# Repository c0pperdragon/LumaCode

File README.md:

# LumaCode
Definition of the "LumaCode" signal standard and documentation of various implementations.

* [Documentation wiki](https://github.com/c0pperdragon/LumaCode/wiki)
* [Issue tracking](https://github.com/c0pperdragon/LumaCode/issues)
* [Reference implementation](signalgenerator)

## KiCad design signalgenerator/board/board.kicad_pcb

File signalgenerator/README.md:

# Signal generator

A small device intended to generate various LumaCode signals. Its main purpose is for developing and
testing decoding/upscaling equipment.

## Usage

The device is powered by 5V over a barrel jack (center positive).
Use the jumper link to select a 50Hz (when jumper closed) or 60Hz (when jumper open) source. 
16 different patterns can be chosen by the 16 combinations of the dip switches.

## Signal possibilites 

The following switch combinations are supported:

1   |  2  | 3   |4    | Signal
--- | --- | --- | --- | -------------------------
OFF | OFF | OFF | OFF | C64/C128
OFF | OFF | OFF | ON  | C64 6567R56A (only 60Hz)
OFF | OFF | ON  | OFF | VIC 20 
OFF | OFF | ON  | ON  | C16, Plus/4
OFF | ON  | OFF | OFF | Atari 8-bit
OFF | ON  | OFF | ON  | Atari 2600 PAL colors
OFF | ON  | ON  | OFF | Atari 2600 NTSC colors
OFF | ON  | ON  | ON  | Atari 7800 
ON  | OFF | OFF | OFF | TMS99xxA
ON  | OFF | OFF | ON  | ZX Spectrum
ON  | OFF | ON  | OFF | NES
ON  | OFF | ON  | ON  | Sega Master System
ON  | ON  | OFF | OFF | Intellivision
ON  | ON  | OFF | ON  | G7000 or Odyssey II
ON  | ON  | ON  | OFF | MC6847
ON  | ON  | ON  | ON  | Lumacode 270p (only 50Hz)

The last option is not used in any actual hardware, but this is an experimental signal with a resolution 
of 480x270 and 6 bits color depth (same color encoding as the Master System). When upscaling by a 
factor of 4, this signal perfectly fits a full-HD screen. Maybe this could be
useful for some tinkering projects.

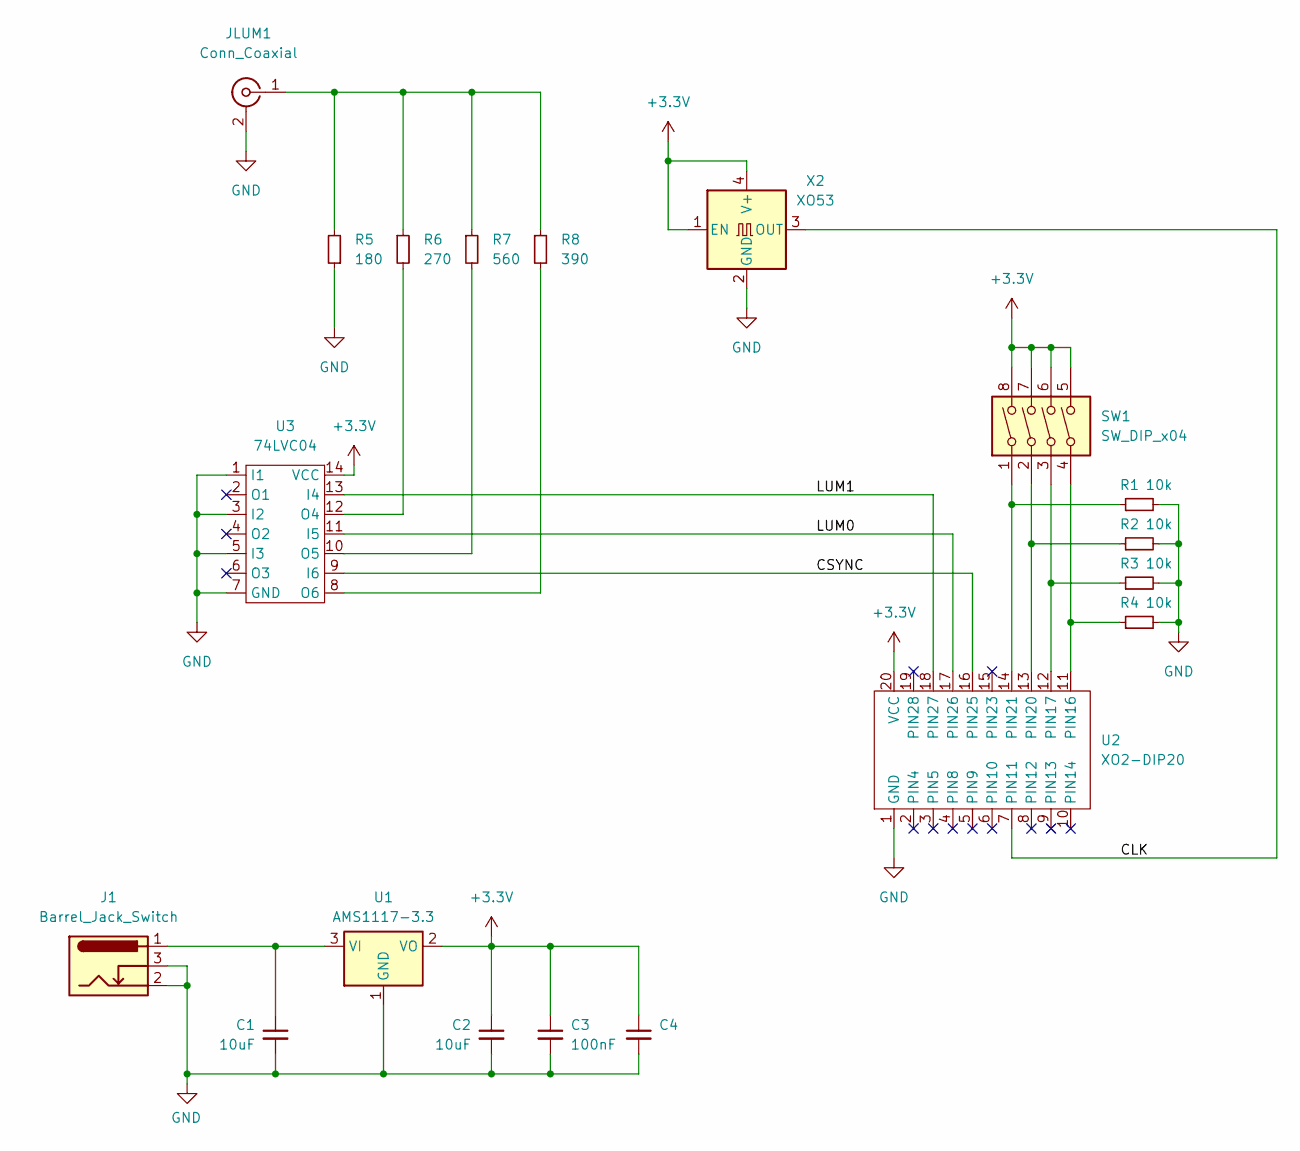
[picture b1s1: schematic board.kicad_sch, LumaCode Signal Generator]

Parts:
C1, C2: 10uF; C_0805_2012Metric_Pad1.18x1.45mm_HandSolder
C3, C4: 100nF; C_0603_1608Metric_Pad1.08x0.95mm_HandSolder
J1: Barrel_Jack_Switch; BarrelJack_Horizontal
JLUM1: Conn_Coaxial; RCA_JACK
R1, R2, R3, R4: 10k; R_0805_2012Metric_Pad1.20x1.40mm_HandSolder
R5: 180; R_0805_2012Metric_Pad1.20x1.40mm_HandSolder
R6: 270; R_0805_2012Metric_Pad1.20x1.40mm_HandSolder
R7: 560; R_0805_2012Metric_Pad1.20x1.40mm_HandSolder
R8: 390; R_0805_2012Metric_Pad1.20x1.40mm_HandSolder
SW1: SW_DIP_x04; DIP-8_W7.62mm
U1: AMS1117-3.3; SOT-223-3_TabPin2
U2: XO2-DIP20; DIP-20_W7.62mm
U3: 74LVC04; TSSOP-14_4.4x5mm_P0.65mm
X2: XO53; Oscillator_SMD_EuroQuartz_XO53-4Pin_5.0x3.2mm

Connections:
+3.3V: C2.1, C3.1, C4.1, SW1.5, SW1.6, SW1.7, SW1.8, U1.2 (VO), U2.20 (VCC), U3.14 (VCC), X2.1 (EN), X2.4 (V+)
/CLK: U2.7 (PIN11), X2.3 (OUT)
/CSYNC: U2.16 (PIN25), U3.9 (I6)
/LUM0: U2.17 (PIN26), U3.11 (I5)
/LUM1: U2.18 (PIN27), U3.13 (I4)
GND: C1.2, C2.2, C3.2, C4.2, J1.2, J1.3, JLUM1.2 (Ext), R1.2, R2.2, R3.2, R4.2, R5.1, U1.1 (GND), U2.1 (GND), U3.1 (I1), U3.3 (I2), U3.5 (I3), U3.7 (GND), X2.2 (GND)
unnamed: JLUM1.1 (In), R5.2, R6.1, R7.1, R8.1
unnamed: C1.1, J1.1, U1.3 (VI)
unnamed: R4.1, SW1.4, U2.11 (PIN16)
unnamed: R3.1, SW1.3, U2.12 (PIN17)
unnamed: R2.1, SW1.2, U2.13 (PIN20)
unnamed: R1.1, SW1.1, U2.14 (PIN21)
unnamed: R6.2, U3.12 (O4)
unnamed: R7.2, U3.10 (O5)
unnamed: R8.2, U3.8 (O6)

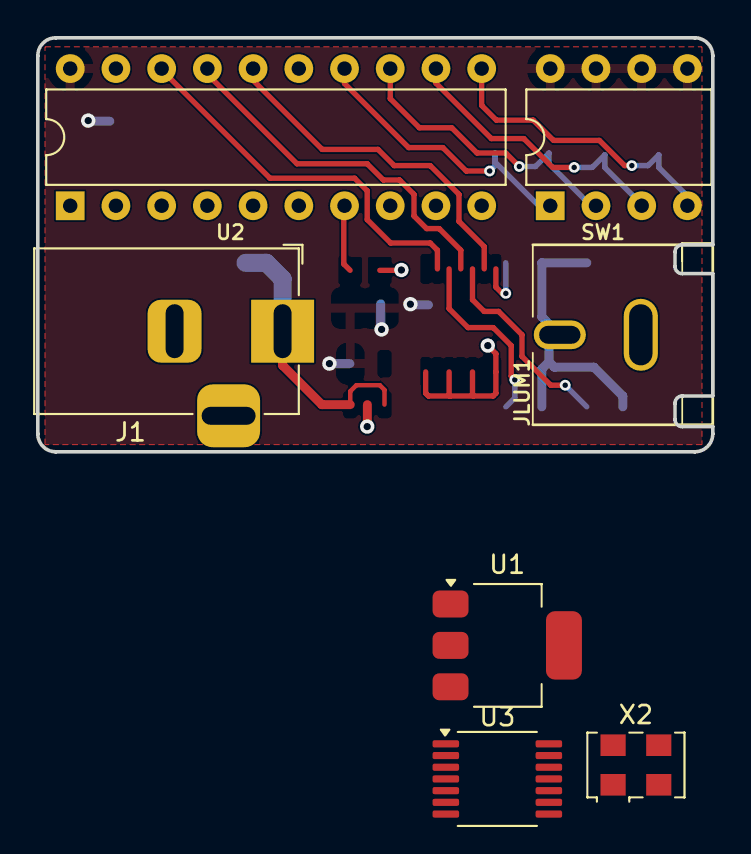
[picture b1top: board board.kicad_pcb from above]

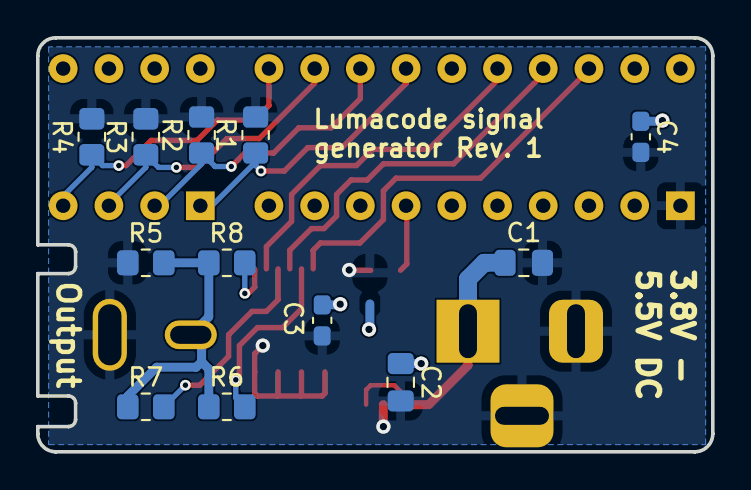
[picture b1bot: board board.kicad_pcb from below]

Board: 2 copper layers, 37.5 x 23.0 mm, 19 parts (12 on the bottom side), 15 nets.

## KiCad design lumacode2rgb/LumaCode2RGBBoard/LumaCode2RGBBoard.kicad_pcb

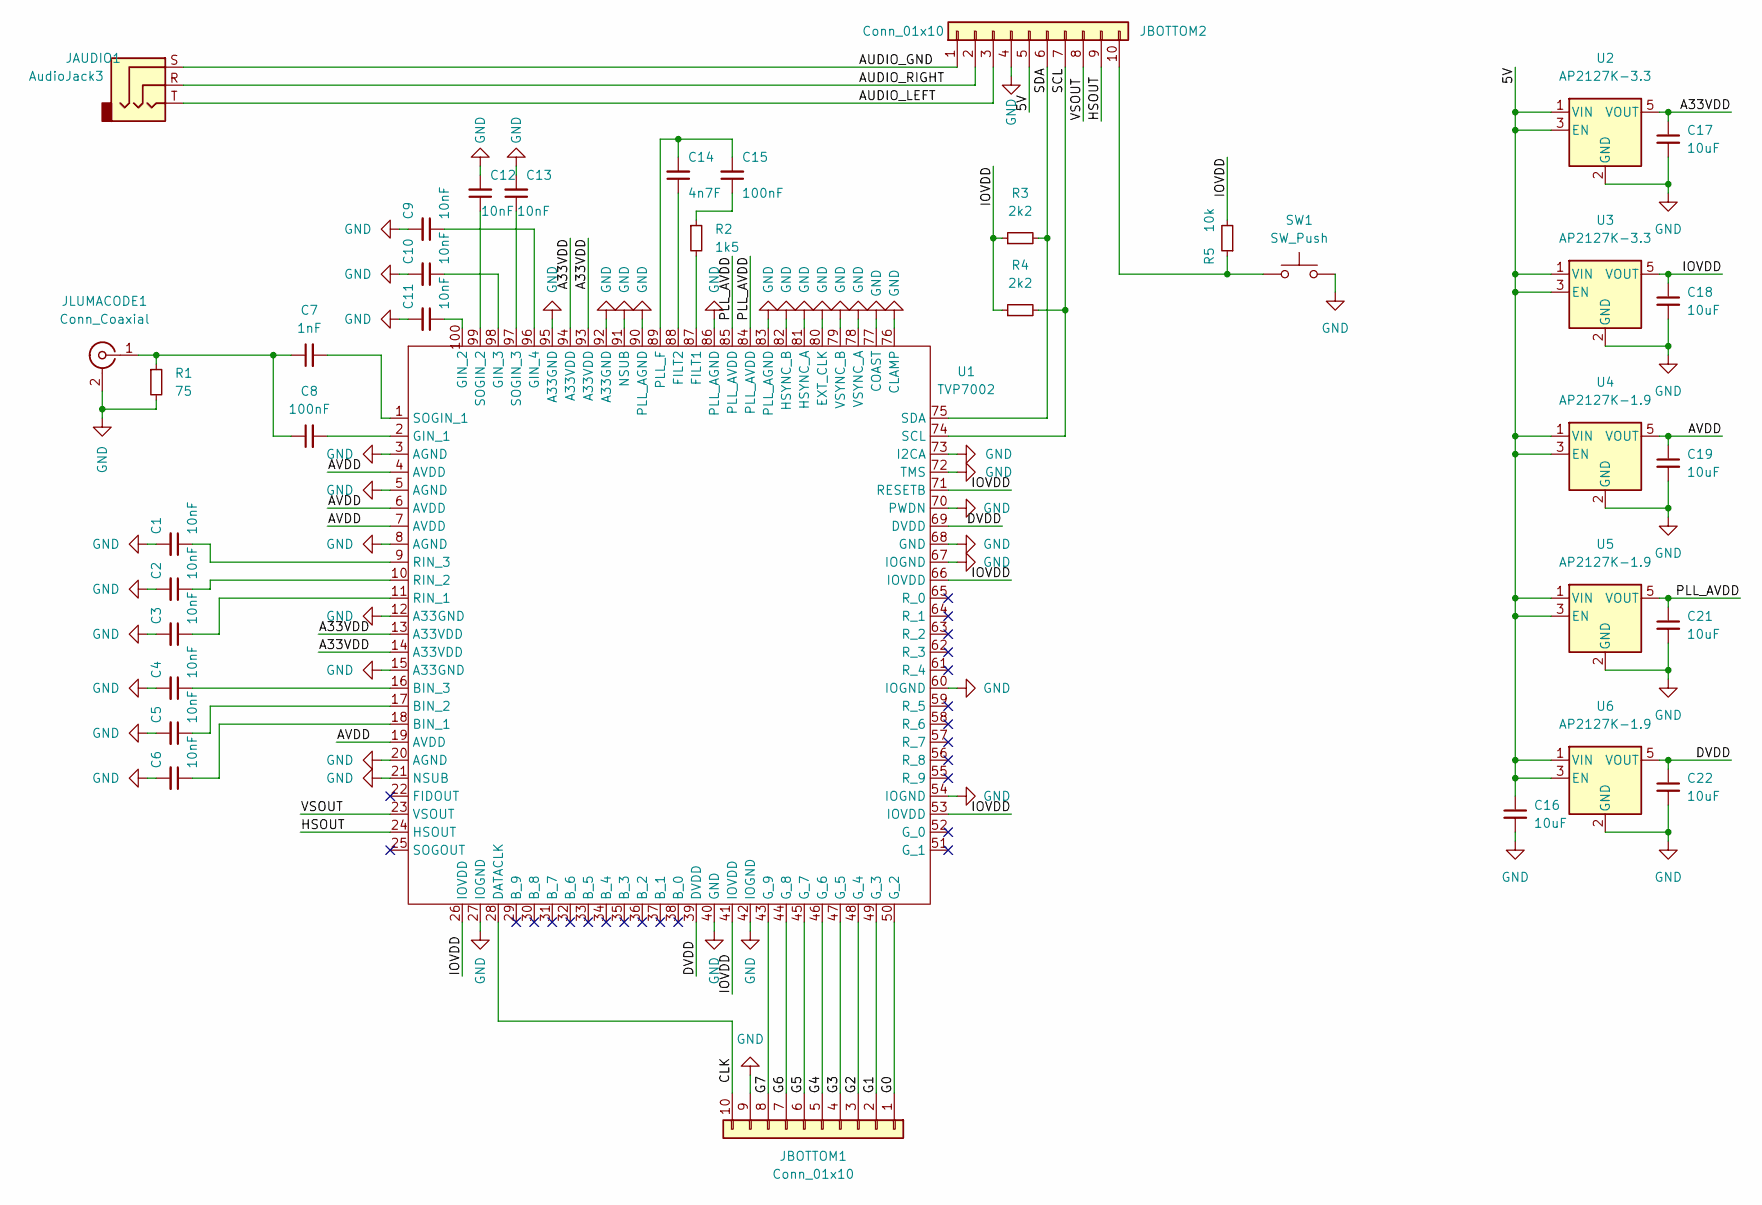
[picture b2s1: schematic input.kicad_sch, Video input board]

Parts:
C1, C2, C3, C4, C5, C6, C9, C10, C11, C12, C13: 10nF; C_0603_1608Metric
C7: 1nF; C_0603_1608Metric
C8, C15: 100nF; C_0603_1608Metric
C14: 4n7F; C_0603_1608Metric
C16, C17, C18, C19, C21, C22: 10uF; C_0805_2012Metric
JAUDIO1: AudioJack3; Jack_3.5mm_Lumberg_1503_07_Horizontal
JBOTTOM1, JBOTTOM2: Conn_01x10; PinHeader_1x10_P2.54mm_Vertical
JLUMACODE1: Conn_Coaxial; RCA_JACK
R1: 75; R_0805_2012Metric
R2: 1k5; R_0805_2012Metric
R3, R4: 2k2; R_0805_2012Metric
R5: 10k; R_0805_2012Metric
SW1: SW_Push; SW_Tactile_SKHH_Angled
U1: TVP7002; TQFP-100-1EP_14x14mm_P0.5mm_EP5x5mm
U2, U3: AP2127K-3.3; SOT-23-5
U4, U5, U6: AP2127K-1.9; SOT-23-5

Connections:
/Input/5V: C16.1, JBOTTOM2.5, U2.1 (VIN), U2.3 (EN), U3.1 (VIN), U3.3 (EN), U4.1 (VIN), U4.3 (EN), U5.1 (VIN), U5.3 (EN), U6.1 (VIN), U6.3 (EN)
/Input/A33VDD: C17.1, U1.13 (A33VDD), U1.14 (A33VDD), U1.93 (A33VDD), U1.94 (A33VDD), U2.5 (VOUT)
/Input/AUDIO_GND: JAUDIO1.S, JBOTTOM2.1
/Input/AUDIO_LEFT: JAUDIO1.T, JBOTTOM2.3
/Input/AUDIO_RIGHT: JAUDIO1.R, JBOTTOM2.2
/Input/AVDD: C19.1, U1.4 (AVDD), U1.6 (AVDD), U1.7 (AVDD), U1.19 (AVDD), U4.5 (VOUT)
/Input/CLK: JBOTTOM1.10, U1.28 (DATACLK)
/Input/DVDD: C22.1, U1.39 (DVDD), U1.69 (DVDD), U6.5 (VOUT)
/Input/G0: JBOTTOM1.1, U1.50 (G_2)
/Input/G1: JBOTTOM1.2, U1.49 (G_3)
/Input/G2: JBOTTOM1.3, U1.48 (G_4)
/Input/G3: JBOTTOM1.4, U1.47 (G_5)
/Input/G4: JBOTTOM1.5, U1.46 (G_6)
/Input/G5: JBOTTOM1.6, U1.45 (G_7)
/Input/G6: JBOTTOM1.7, U1.44 (G_8)
/Input/G7: JBOTTOM1.8, U1.43 (G_9)
/Input/HSOUT: JBOTTOM2.9, U1.24 (HSOUT)
/Input/IOVDD: C18.1, R3.1, R4.1, R5.2, U1.26 (IOVDD), U1.41 (IOVDD), U1.53 (IOVDD), U1.66 (IOVDD), U1.71 (RESETB), U3.5 (VOUT)
/Input/PLL_AVDD: C21.1, U1.84 (PLL_AVDD), U1.85 (PLL_AVDD), U5.5 (VOUT)
/Input/SCL: JBOTTOM2.7, R4.2, U1.74 (SCL)
/Input/SDA: JBOTTOM2.6, R3.2, U1.75 (SDA)
/Input/VSOUT: JBOTTOM2.8, U1.23 (VSOUT)
GND: C1.2, C2.2, C3.2, C4.2, C5.2, C6.2, C9.2, C10.2, C11.2, C12.2, C13.2, C16.2, C17.2, C18.2, C19.2, C21.2, C22.2, JBOTTOM1.9, JBOTTOM2.4, JLUMACODE1.2 (Ext), R1.2, SW1.2, U1.3 (AGND), U1.5 (AGND), U1.8 (AGND), U1.12 (A33GND), U1.15 (A33GND), U1.20 (AGND), U1.21 (NSUB), U1.27 (IOGND), U1.40 (GND), U1.42 (IOGND), U1.54 (IOGND), U1.60 (IOGND), U1.67 (IOGND), U1.68 (GND), U1.70 (PWDN), U1.72 (TMS), U1.73 (I2CA), U1.76 (CLAMP), U1.77 (COAST), U1.78 (VSYNC_A), U1.79 (VSYNC_B), U1.80 (EXT_CLK), U1.81 (HSYNC_A), U1.82 (HSYNC_B), U1.83 (PLL_AGND), U1.86 (PLL_AGND), U1.90 (PLL_AGND), U1.91 (NSUB), U1.92 (A33GND), U1.95 (A33GND), U2.2 (GND), U3.2 (GND), U4.2 (GND), U5.2 (GND), U6.2 (GND); also elsewhere on the board
unnamed: C1.1, U1.9 (RIN_3)
unnamed: C2.1, U1.10 (RIN_2)
unnamed: C3.1, U1.11 (RIN_1)
unnamed: C4.1, U1.16 (BIN_3)
unnamed: C5.1, U1.17 (BIN_2)
unnamed: C6.1, U1.18 (BIN_1)
unnamed: C7.1, C8.1, JLUMACODE1.1 (In), R1.1
unnamed: C7.2, U1.1 (SOGIN_1)
unnamed: C8.2, U1.2 (GIN_1)
unnamed: C9.1, U1.96 (GIN_4)
unnamed: C10.1, U1.98 (GIN_3)
unnamed: C11.1, U1.100 (GIN_2)
unnamed: C12.1, U1.99 (SOGIN_2)
unnamed: C13.1, U1.97 (SOGIN_3)
unnamed: C14.1, U1.88 (FILT2)
unnamed: C14.2, C15.2, U1.89 (PLL_F)
unnamed: C15.1, R2.1
unnamed: JBOTTOM2.10, R5.1, SW1.1
unnamed: R2.2, U1.87 (FILT1)

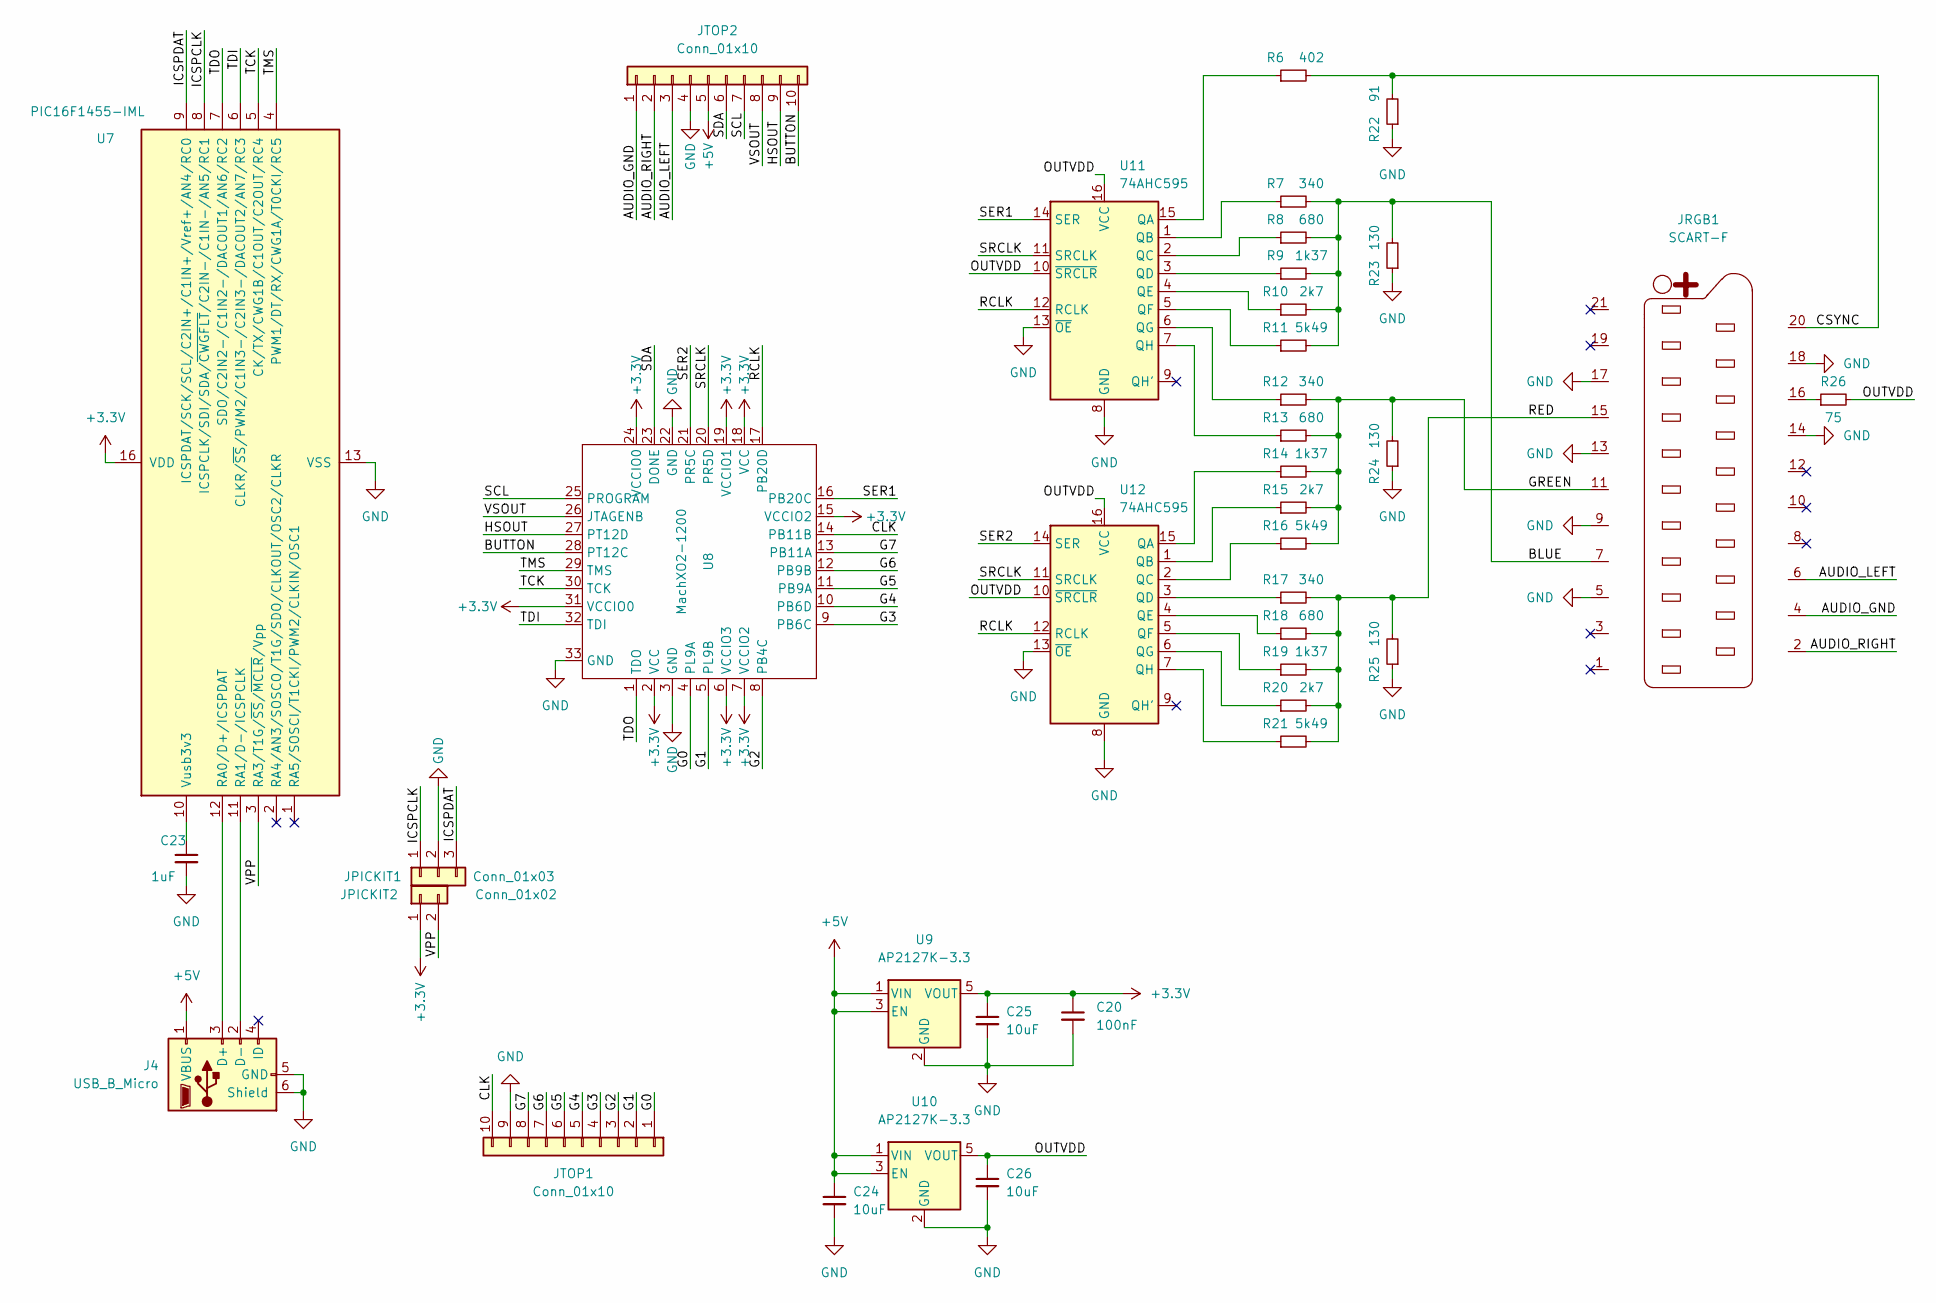
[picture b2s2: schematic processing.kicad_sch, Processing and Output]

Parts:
C20: 100nF; C_0603_1608Metric
C23: 1uF; C_0805_2012Metric
C24, C25, C26: 10uF; C_0805_2012Metric
J4: USB_B_Micro; USB_Micro-B_Amphenol_10104110_Horizontal
JPICKIT1: Conn_01x03; PinHeader_1x03_P2.54mm_Vertical
JPICKIT2: Conn_01x02; PinHeader_1x02_P2.54mm_Vertical
JRGB1: SCART-F; SCART_Edge_mount
JTOP1, JTOP2: Conn_01x10; PinHeader_1x10_P2.54mm_Vertical
R6: 402; R_0603_1608Metric
R7, R12, R17: 340; R_0603_1608Metric
R8, R13, R18: 680; R_0603_1608Metric
R9, R14, R19: 1k37; R_0603_1608Metric
R10, R15, R20: 2k7; R_0603_1608Metric
R11, R16, R21: 5k49; R_0603_1608Metric
R22: 91; R_0603_1608Metric
R23, R24, R25: 130; R_0603_1608Metric
R26: 75; R_0805_2012Metric
U7: PIC16F1455-IML; QFN-16-1EP_4x4mm_P0.65mm_EP2.1x2.1mm
U8: MachXO2-1200; QFN-32-1EP_5x5mm_P0.5mm_EP3.1x3.1mm_ThermalVias
U9, U10: AP2127K-3.3; SOT-23-5
U11, U12: 74AHC595; TSSOP-16_4.4x5mm_P0.65mm

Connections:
+3.3V: C20.1, C25.1, JPICKIT2.1, U7.16 (VDD), U8.2 (VCC), U8.6 (VCCIO3), U8.7 (VCCIO2), U8.15 (VCCIO2), U8.18 (VCC), U8.19 (VCCIO1), U8.24 (VCCIO0), U8.31 (VCCIO0), U9.5 (VOUT)
+5V: C24.1, J4.1 (VBUS), JTOP2.5, U9.1 (VIN), U9.3 (EN), U10.1 (VIN), U10.3 (EN)
/Processing/AUDIO_GND: JRGB1.4, JTOP2.1
/Processing/AUDIO_LEFT: JRGB1.6, JTOP2.3
/Processing/AUDIO_RIGHT: JRGB1.2, JTOP2.2
/Processing/BLUE: JRGB1.7, R7.2, R8.2, R9.2, R10.2, R11.2, R23.2
/Processing/BUTTON: JTOP2.10, U8.28 (PT12C)
/Processing/CLK: JTOP1.10, U8.14 (PB11B)
/Processing/CSYNC: JRGB1.20, R6.2, R22.2
/Processing/G0: JTOP1.1, U8.4 (PL9A)
/Processing/G1: JTOP1.2, U8.5 (PL9B)
/Processing/G2: JTOP1.3, U8.8 (PB4C)
/Processing/G3: JTOP1.4, U8.9 (PB6C)
/Processing/G4: JTOP1.5, U8.10 (PB6D)
/Processing/G5: JTOP1.6, U8.11 (PB9A)
/Processing/G6: JTOP1.7, U8.12 (PB9B)
/Processing/G7: JTOP1.8, U8.13 (PB11A)
/Processing/GREEN: JRGB1.11, R12.2, R13.2, R14.2, R15.2, R16.2, R24.2
/Processing/HSOUT: JTOP2.9, U8.27 (PT12D)
/Processing/ICSPCLK: JPICKIT1.1, U7.8 (ICSPCLK/SDI/SDA/~CWGFLT/C2IN-/C1IN-/AN5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)
/Processing/ICSPDAT: JPICKIT1.3, U7.9 (ICSPDAT/SCK/SCL/C2IN+/C1IN+/Vref+/AN4/R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)
/Processing/OUTVDD: C26.1, R26.2, U10.5 (VOUT), U11.10 (~SRCLR), U11.16 (VCC), U12.10 (~SRCLR), U12.16 (VCC)
/Processing/RCLK: U8.17 (PB20D), U11.12 (RCLK), U12.12 (RCLK)
/Processing/RED: JRGB1.15, R17.2, R18.2, R19.2, R20.2, R21.2, R25.2
/Processing/SCL: JTOP2.7, U8.25 (PROGRAM)
/Processing/SDA: JTOP2.6, U8.23 (DONE)
/Processing/SER1: U8.16 (PB20C), U11.14 (SER)
/Processing/SER2: U8.21 (PR5C), U12.14 (SER)
/Processing/SRCLK: U8.20 (PR5D), U11.11 (SRCLK), U12.11 (SRCLK)
/Processing/TCK: U7.5 (CK/TX/CWG1B/C1OUT/C2OUT/RC4), U8.30 (TCK)
/Processing/TDI: U7.6 (CLKR/~SS/PWM2/C1IN3-/C2IN3-/DACOUT2/AN7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), U8.32 (TDI)
/Processing/TDO: U7.7 (SDO/C2IN2-/C1IN2-/DACOUT1/AN6/RC2), U8.1 (TDO)
/Processing/TMS: U7.4 (PWM1/DT/RX/CWG1A/T0CKI/RC5), U8.29 (TMS)
/Processing/VPP: JPICKIT2.2, U7.3 (RA3/T1G/~SS/~MCLR/Vpp)
/Processing/VSOUT: JTOP2.8, U8.26 (JTAGENB)
GND: C20.2, C23.2, C24.2, C25.2, C26.2, J4.5 (GND), J4.6 (Shield), JPICKIT1.2, JRGB1.5, JRGB1.9, JRGB1.13, JRGB1.14, JRGB1.17, JRGB1.18, JTOP1.9, JTOP2.4, R22.1, R23.1, R24.1, R25.1, U7.13 (VSS), U8.3 (GND), U8.22 (GND), U8.33 (GND), U9.2 (GND), U10.2 (GND), U11.8 (GND), U11.13 (~OE), U12.8 (GND), U12.13 (~OE); also elsewhere on the board
unnamed: C23.1, U7.10 (Vusb3v3)
unnamed: J4.2 (D-), U7.11 (RA1/D-/ICSPCLK)
unnamed: J4.3 (D+), U7.12 (RA0/D+/ICSPDAT)
unnamed: JRGB1.16, R26.1
unnamed: R6.1, U11.15 (QA)
unnamed: R7.1, U11.1 (QB)
unnamed: R8.1, U11.2 (QC)
unnamed: R9.1, U11.3 (QD)
unnamed: R10.1, U11.4 (QE)
unnamed: R11.1, U11.5 (QF)
unnamed: R12.1, U11.6 (QG)
unnamed: R13.1, U11.7 (QH)
unnamed: R14.1, U12.15 (QA)
unnamed: R15.1, U12.1 (QB)
unnamed: R16.1, U12.2 (QC)
unnamed: R17.1, U12.3 (QD)
unnamed: R18.1, U12.4 (QE)
unnamed: R19.1, U12.5 (QF)
unnamed: R20.1, U12.6 (QG)
unnamed: R21.1, U12.7 (QH)

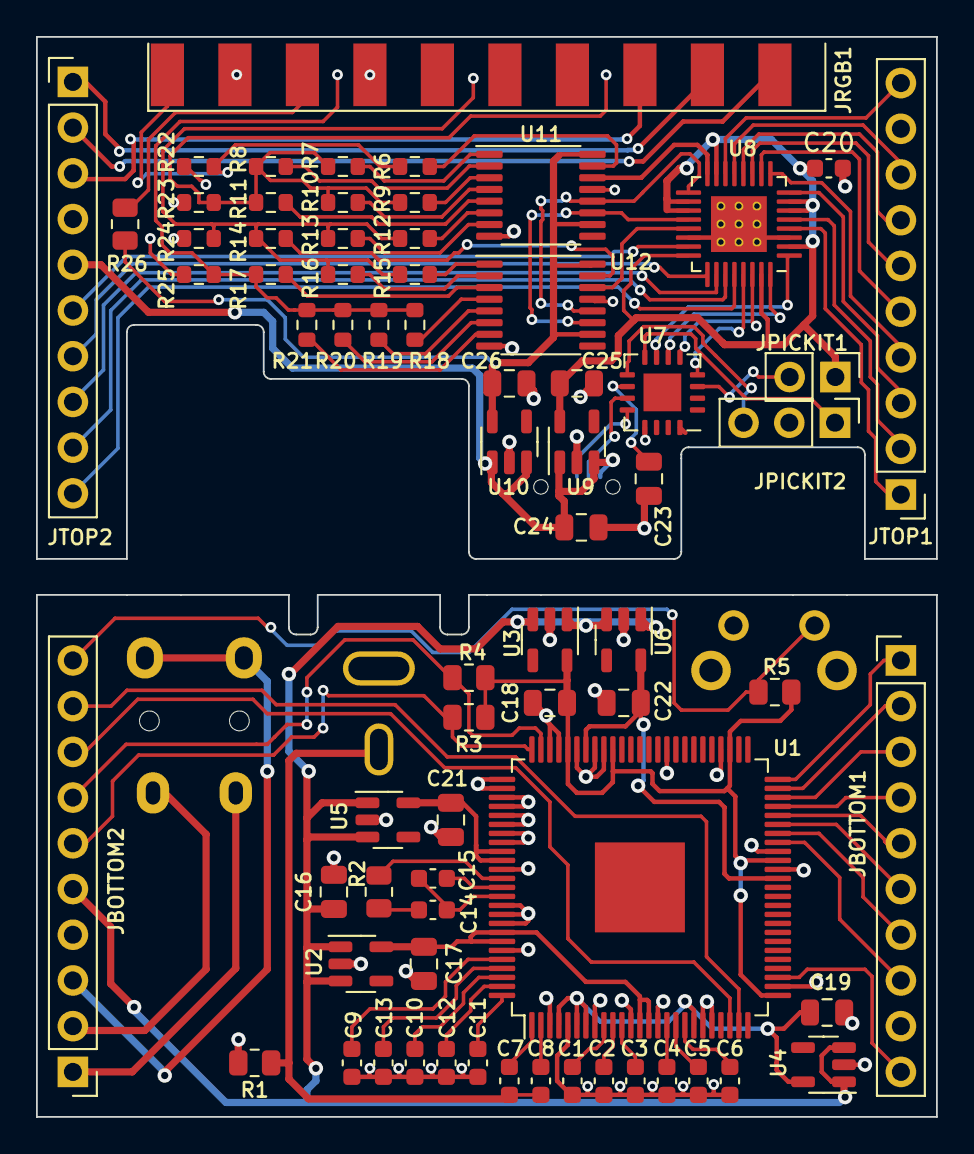
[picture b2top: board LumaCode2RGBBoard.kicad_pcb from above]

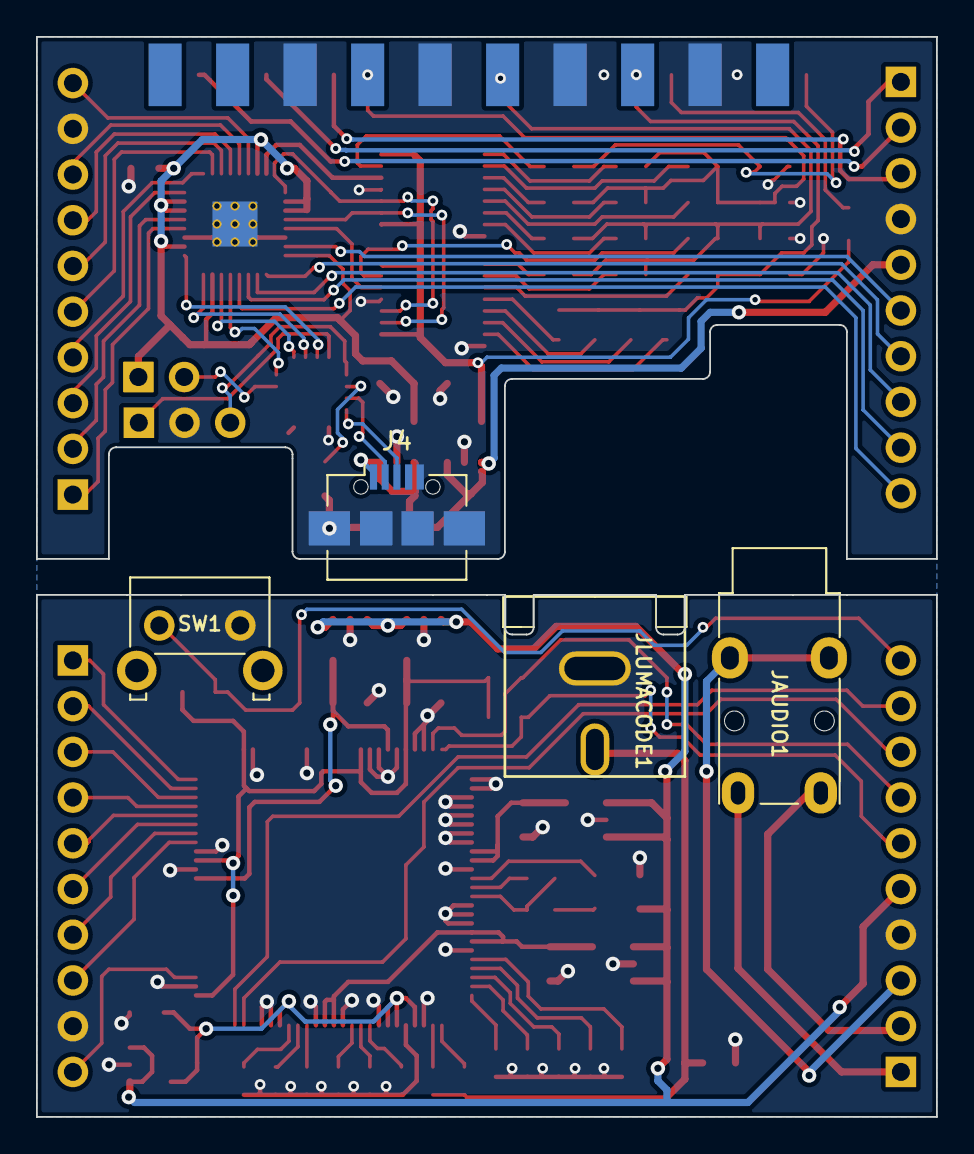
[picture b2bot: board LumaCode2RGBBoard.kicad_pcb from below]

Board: 2 copper layers, 50.0 x 60.0 mm, 75 parts (4 on the bottom side), 97 nets.

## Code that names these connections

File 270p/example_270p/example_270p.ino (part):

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
// pin  port   usage
// 13   PA3    EXTCLK (24 MHz)
// 11   PA1    CSYNC    680 Ohm
// 9    PB0    LUM0    1000 Ohm
// 8    PB1    LUM1     470 Ohm

PROGMEM const byte picture[256*48] = {
  #include "picture.h"
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
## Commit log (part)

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2023-06-22 Test signal generator
2023-06-22 Restructure documentation
2023-06-22 Fix parentesis
2023-06-30 Signal generator dummy code
2023-06-30 Fix link
2023-07-01 Reference board schematic
2023-07-01 Refactor clock generator
2023-07-02 Dynamic reconfiguration of the PLL
2023-07-03 Create C64 output pattern for PAL and NTSC
2023-07-04 Atari 8-bit pattern
2023-07-06 Fix timing of VIC20 signals
2023-07-07 VIC 20 pixel pattern
2023-08-28 Test rig board
2023-08-31 Test rig example code
2023-08-31 ignore generated files
2023-08-31 Use crystal oscillator instead of internal oscillator
2023-09-02 Digital test signals to drive the TIAdigitizer
2023-09-05 Calcuation for VIC20 test rig PLL
2023-09-09 Use test rig to generate a 100 MHz clock
2023-09-13 Board design LumaCode2RGB
2023-09-14 Schematic and start PCB layout
2023-09-15 PCB layout
2023-09-16 Squeeze all components onto the PCB
2023-09-17 Restructure Repos
2023-09-20 Make a 14.3 Mhz differential signal clock
2023-09-20 Fix clock
2023-11-28 Generate Atari 2600 signal
2024-05-06 Add direct output pin for fast path
2024-06-03 PCB for signal generator
2024-06-04 Support more machines
2024-06-04 Find tune picture alignment Add Speccy logo
2024-06-06 Implement signals for all machines (need more fine-tuning)
2024-06-06 Tweak timing and geometry of test signal
2024-06-24 Implement NES signal PAL/NTSC
2024-06-24 Modify position
2024-06-25 Skip half-pixels in NES NTSC signal
2024-06-25 Fine-tune screen position
2024-08-12 Implement XOR sync in signal pattern
2024-08-15 Test signal VSYNC, HSYNC
2024-08-19 Add info on planned product portfolio
2024-10-27 pll calculation for new NES signal generator
2024-11-12 Small implementation to fine-tune the Amiga system clock
2024-11-19 Cabletester firmware
2024-11-21 Adjust test image
2024-11-24 Define Lumacode270p signal
2024-11-27 Title for each output mode
2024-11-27 RGBtoHDMI profiles
2024-11-28 Use 312 lines for Lumacode720p50
2024-11-28 Update specs for Lumacode270p
2024-12-03 Create test image in 270p
2024-12-04 Use stack to prepare image data for b&w picture
2024-12-05 Finish demo picture
2025-01-20 Create 4 levels of each R,G,B to test Analog RGBtoHDMI
2025-04-26 Add G7000 test signal
2025-04-27 Add potential Atari 7800 lumacode signal.
2025-05-06 Change signal generation for Maria
2025-05-07 Fine-tune signal and sync timings for Maria signal
2025-07-17 Add mode switch
2025-08-08 Reword cable tester to allow for new features.
2025-08-09 Adjust profiles for various cables on the tester.
2025-08-13 Modify the cable tester to work with the ZX Spectrum 128 cable.
2025-08-20 Atari 7800 PAL has different pixel clock
2025-09-30 Binaries
2025-10-07 Test picture for Amiga for Analog RGBtoHDMI
2025-10-22 Fix EGA signal generator to match Mode2-80
2025-10-23 Test signal for Apple II
2025-10-25 Experimental Apple II signal
2025-10-25 Keep color burst even in bottmm high-res lines, but reduce DC voltage (but not peek-to-peek).
2025-11-04 Various signal patterns for EGA,CGA,MDA
2025-11-13 Provide csync on extra pin
2025-12-09 Test signal of Atari ST Monochrome
2025-12-09 Fix sync polarity
2026-01-16 Add files for printing the device case
2026-02-01 Implement additional signal formats
2026-02-02 Signal generator docu
2026-02-02 Fix readme
2026-02-02 Typo
2026-02-02 better pictures
2026-03-10 New TEDdigitizer lumacode format
2026-03-15 Tweak lumacode encoding for the TED
2026-05-17 Monochrome picture to test interlaced mode processing
2026-05-30 Test signal that should match what I plan to bring out of the gameboy.
2026-06-06 Provide non-inverting code to allow use of LVC245
2026-06-12 Test pictures
